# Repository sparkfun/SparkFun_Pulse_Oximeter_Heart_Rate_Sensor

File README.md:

SparkFun Pulse Oximeter and Heart Rate Monitor 
========================================

[*SparkFun Pulse Oximeter and Heart Rate Monitor (SEN-15291)*](https://www.sparkfun.com/products/15219)

The SparkFun Pulse Oximeter and Heart-Rate Sensor is an I&sup2;C based [biometric](https://en.wikipedia.org/wiki/Biometrics) sensor, utilizing two chips from Maxim Integrated: 
the MAX32664 Bio Metric Sensor Hub and the MAX30101 Pulse Oximetry and Heart-Rate Module.

The MAX30101 does all the sensing by utilizing its' internal LEDs to bounce light off the arteries and arterioles in your finger's subcutaneous layer and sensing how much light 
is absorbed with its' photodetectors . This is known as [photoplethysmography](https://en.wikipedia.org/wiki/Photoplethysmogram). This data is passed onto and analyzed by the 
MAX32664 which applies its' algorithms to determine heart rate and blood oxygen saturation (SpO2). The embedded algorithm uses digital filtering, pressure/position compensation, 
advanced R-wave detection and automatic gain control to determine the heart rate in beats per minute while minimizing power.  SpO2 results are reported as percentage of hemoglobin 
that is saturated with oxygen. It also provides useful information such as the sensor's confidence in its' reportings as well as a handy finger detection data point. To get the 
most out of the sensor we've written an Arduino Library to make it easy to adjust all the possible configurations.

Repository Contents
-------------------

* **/Documentation** - Data sheets and additional product information.
* **/Firmware** - Programming File for the MAX32664 
* **/Hardware** - Eagle design files (.brd, .sch)
* **/Production** - Production panel files (.brd)

Documentation
--------------
* **[Arduino Library](https://github.com/sparkfun/SparkFun_Bio_Sensor_Hub_Library)** - Arduino Library with Example Sketches
* **[Hookup Guide](https://learn.sparkfun.com/tutorials/sparkfun-pulse-oximeter-and-heart-rate-monitor-hookup-guide)** - Basic hookup guide for the SparkFun Pulse Oximeter and Heart Rate Sensor.

Product Versions
----------------
* [SEN-15291](https://www.sparkfun.com/products/15219)- SparkFun Version 1.0

License Information
-------------------

This product is _**open source**_! 

Please review the LICENSE.md file for license information. 

If you have any questions or concerns on licensing, please contact technical support on our [SparkFun forums](https://forum.sparkfun.com/viewforum.php?f=152).

Distributed as-is; no warranty is given.

- Your friends at SparkFun.

_<COLLABORATION CREDIT>_

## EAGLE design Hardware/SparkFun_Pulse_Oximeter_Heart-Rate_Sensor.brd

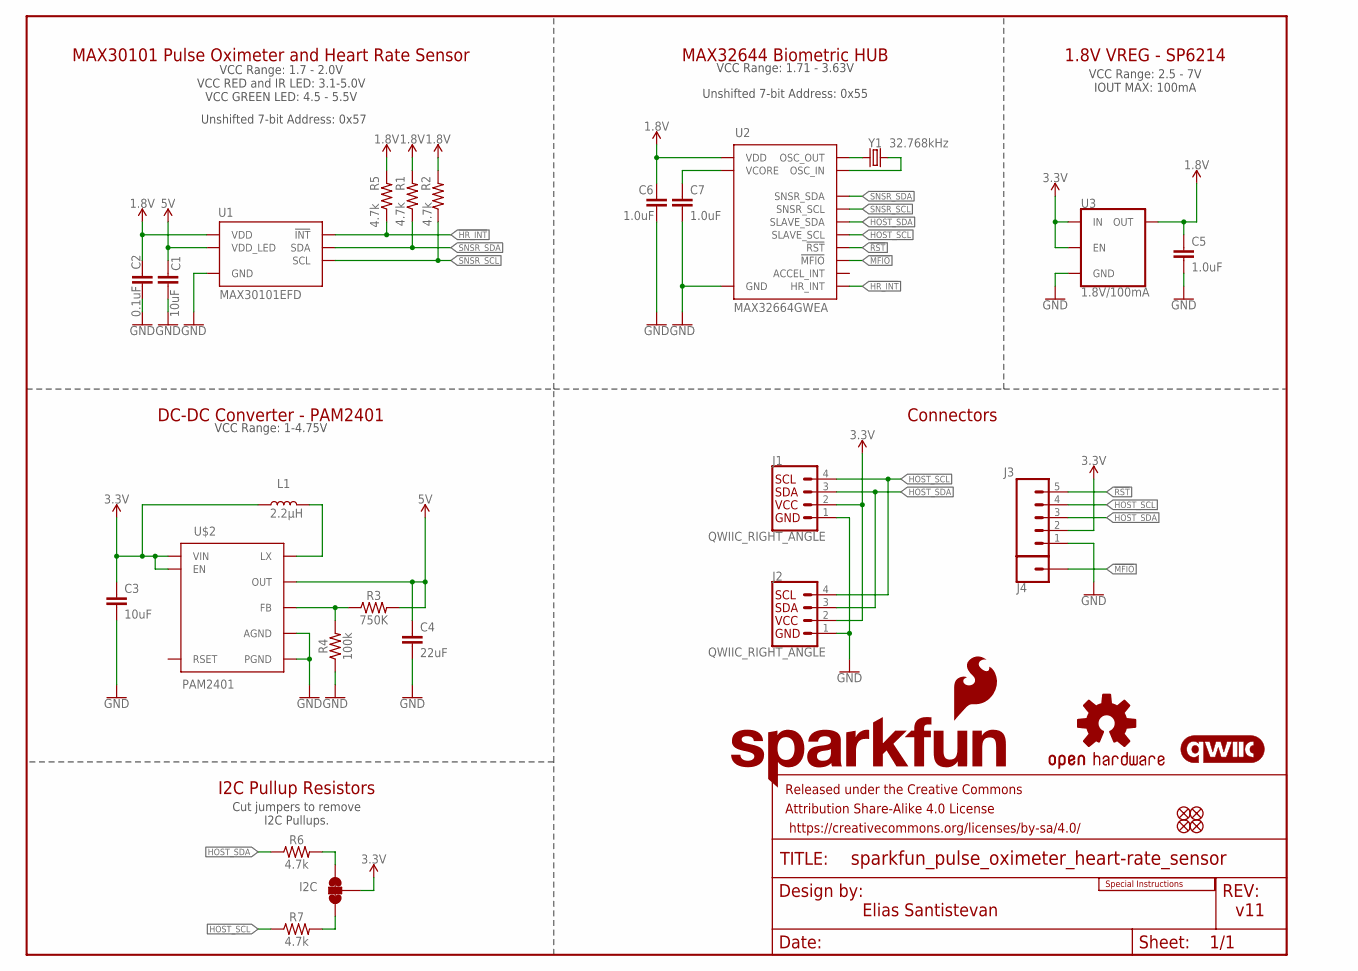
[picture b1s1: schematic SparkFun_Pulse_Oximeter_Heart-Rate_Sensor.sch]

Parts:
C1, C3: 10uF; 0603
C2: 0.1uF; 0402-TIGHT
C4: 22uF; 0805
C5: 1.0uF; 0603
C6, C7: 1.0uF; 0402-TIGHT
FD1, FD2, FD3, FD4: FIDUCIALUFIDUCIAL; FIDUCIAL-MICRO
FRAME1: FRAME-LETTER; CREATIVE_COMMONS
I2C: JUMPER-SMT_3_2-NC_TRACE_SILK; SMT-JUMPER_3_2-NC_TRACE_SILK
J1, J2: QWIIC_RIGHT_ANGLE; JST04_1MM_RA
J3: CONN_05NO_SILK; 1X05_NO_SILK
J4: CONN_01PTH_NO_SILK_YES_STOP; 1X01_NO_SILK
L1: 2.2μH; 0806
LOGO1: SFE_LOGO_FLAME.1_INCH; SFE_LOGO_FLAME_.1
LOGO2: OSHW-LOGOMINI; OSHW-LOGO-MINI
LOGO3: SFE_LOGO_NAME.1_INCH; SFE_LOGO_NAME_.1
LOGO4: SPECIAL_INSTRUCTIONS-ORDERING; ORDERING_INSTRUCTIONS
LOGO5: QWIIC_LOGO_4MM; QWIIC_4MM
R1, R2, R5, R6, R7: 4.7k; 0603
R3: 750K; 0603
R4: 100k; 0402-TIGHT
U1: MAX30101EFD; 14_PIN_OESIP
U2: MAX32664GWEA; 16_PIN_WLP
U3: 1.8V/100mA; SC70
U$2: PAM2401; MSOP8
Y1: 32.768kHz; CRYSTAL-SMD-3.2X1.5MM

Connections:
1.8V: C2.1, C5.1, C6.1, R1.2, R2.2, R5.2, U1.P11 (VDD), U2.3 (VDD), U3.5 (OUT)
3.3V: C3.1, I2C.2, J1.2, J2.2, J3.2, L1.1, U3.1 (IN), U3.3 (EN), U$2.2 (EN), U$2.3 (VIN)
5V: C1.1, C4.1, R3.2, U1.P9 (VDD_LED), U1.P10 (VDD_LED), U$2.7 (OUT)
!HR_INT: R5.1, U1.P13 (!INT), U2.6 (HR_INT)
!MFIO: J4.1, U2.16 (!MFIO)
!RST: J3.5, U2.12 (!RST)
GND: C1.2, C2.2, C3.2, C4.2, C5.2, C6.2, C7.2, J1.1, J2.1, J3.1, R4.1, U1.P4 (GND), U1.P12 (GND), U2.13 (GND), U3.2 (GND), U$2.4 (AGND), U$2.8 (PGND)
HOST_SCL: J1.4, J2.4, J3.4, R7.1, U2.10 (SLAVE_SCL)
HOST_SDA: J1.3, J2.3, J3.3, R6.1, U2.9 (SLAVE_SDA)
unnamed: C7.1, U2.4 (VCORE)
unnamed: R3.1, R4.2, U$2.5 (FB)
unnamed: L1.2, U$2.1 (LX)
unnamed: I2C.3, R6.2
unnamed: I2C.1, R7.2
unnamed: U2.1 (OSC_OUT), Y1.P$1 (1)
unnamed: U2.2 (OSC_IN), Y1.P$2 (2)
SNSR_SCL: R2.1, U1.P2 (SCL), U2.5 (SNSR_SCL)
SNSR_SDA: R1.1, U1.P3 (SDA), U2.14 (SNSR_SDA)

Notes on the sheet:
Elias Santistevan
v11
VCC Range: 1.71 - 3.63V
Unshifted 7-bit Address: 0x55
MAX30101 Pulse Oximeter and Heart Rate Sensor
MAX32644 Biometric HUB
1.8V VREG - SP6214
DC-DC Converter - PAM2401
Connectors
I2C Pullup Resistors
VCC Range: 1.7 - 2.0V VCC RED and IR LED: 3.1-5.0V VCC GREEN LED: 4.5 - 5.5V
Unshifted 7-bit Address: 0x57
VCC Range: 2.5 - 7V IOUT MAX: 100mA
VCC Range: 1-4.75V
Cut jumpers to remove I2C Pullups.

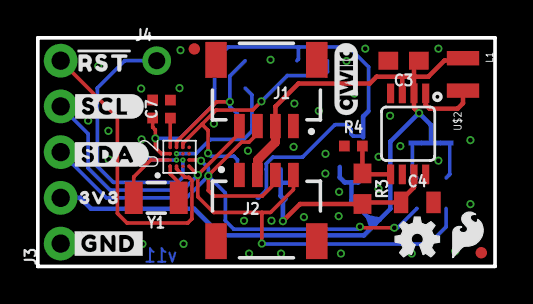
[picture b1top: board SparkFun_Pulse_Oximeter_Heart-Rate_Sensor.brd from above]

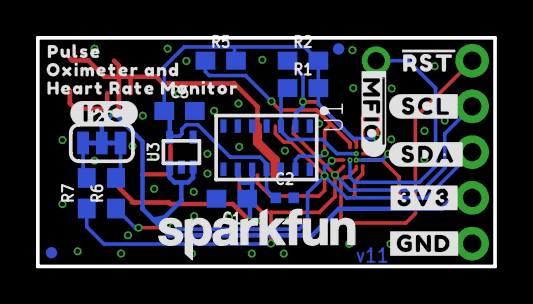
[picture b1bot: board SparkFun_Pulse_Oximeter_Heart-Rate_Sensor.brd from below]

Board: 2 copper layers, 25.4 x 12.7 mm, 50 parts (24 on the bottom side), 18 nets.

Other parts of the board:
U$1: #I2C#1348
U$3, U$5: #GND#0
U$4: #SCL#7
U$6, U$12: #RST#32
U$7: 3V338
U$8: #SDA#10
U$9: #3V3#1
U$10: #SDA#9
U$11: #SCL#9
U$13: ##MFIO##12
U$17: PULSE35
U$20: OXIMETER_AND36
U$21: HEART_RATE_MONITOR37

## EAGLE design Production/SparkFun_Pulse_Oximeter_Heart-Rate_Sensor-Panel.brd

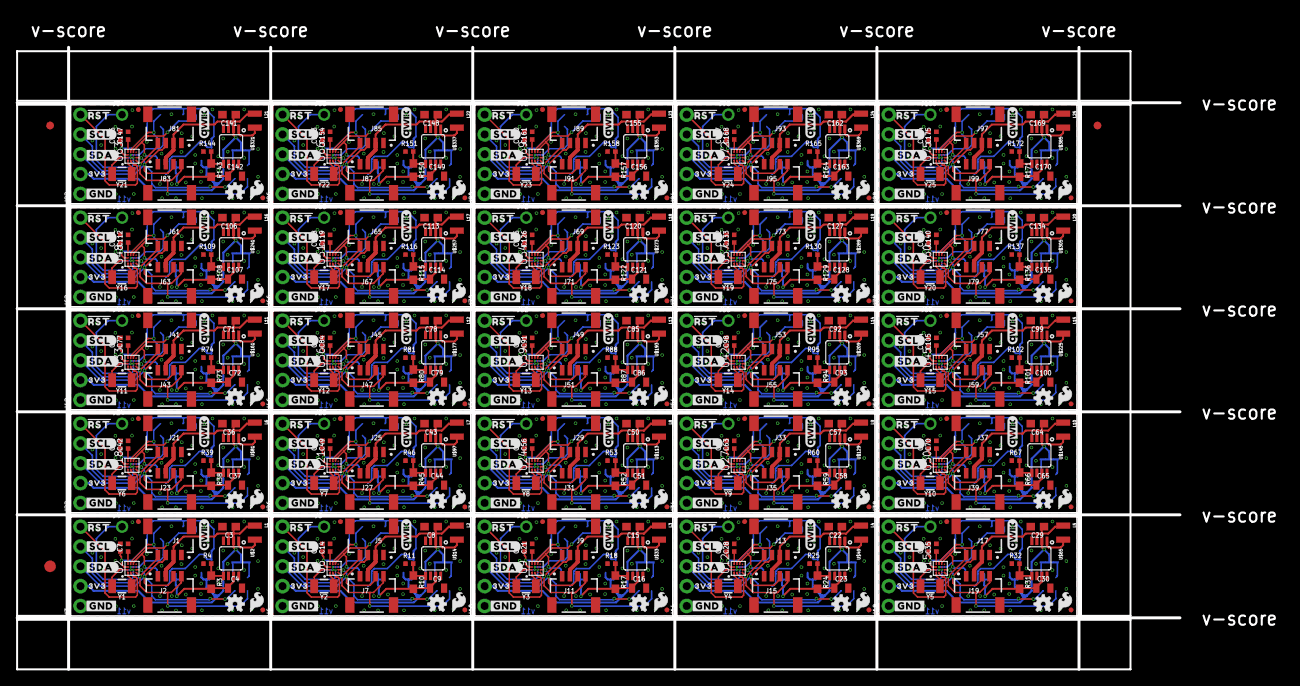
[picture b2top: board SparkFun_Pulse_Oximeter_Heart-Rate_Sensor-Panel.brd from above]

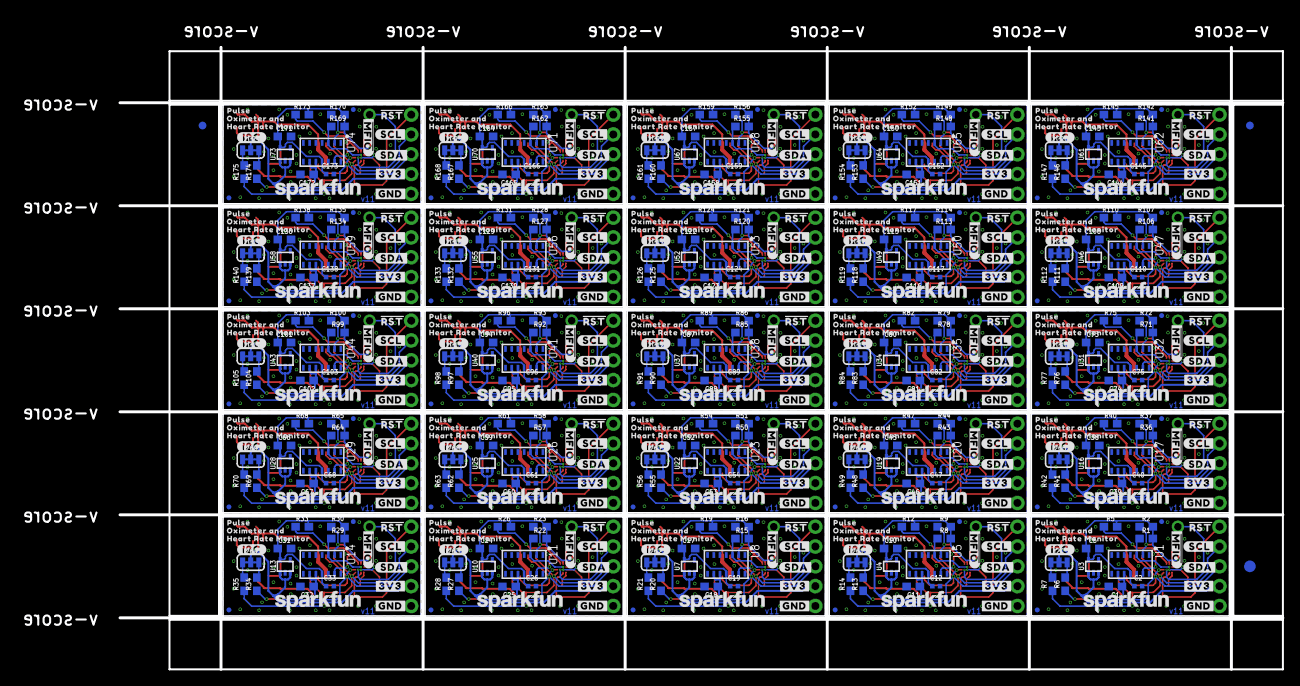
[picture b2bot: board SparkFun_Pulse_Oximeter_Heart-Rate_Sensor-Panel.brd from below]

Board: 2 copper layers, 162.3 x 83.6 mm, 1206 parts (603 on the bottom side), 450 nets.

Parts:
C1, C3, C8, C11, C15, C18, C22, C25, C29, C32, C36, C39, C43, C46, C50, C53, C57, C60, C64, C67, C71, C74, C78, C81, C85, C88, C92, C95, C99, C102, C106, C109, C113, C116, C120, C123, C127, C130, C134, C137, C141, C144, C148, C151, C155, C158, C162, C165, C169, C172: 10uF; 0603
C2, C12, C19, C26, C33, C40, C47, C54, C61, C68, C75, C82, C89, C96, C103, C110, C117, C124, C131, C138, C145, C152, C159, C166, C173: 0.1uF; 0402-TIGHT
C4, C9, C16, C23, C30, C37, C44, C51, C58, C65, C72, C79, C86, C93, C100, C107, C114, C121, C128, C135, C142, C149, C156, C163, C170: 22uF; 0805
C5, C10, C17, C24, C31, C38, C45, C52, C59, C66, C73, C80, C87, C94, C101, C108, C115, C122, C129, C136, C143, C150, C157, C164, C171: 1.0uF; 0603
C6, C7, C13, C14, C20, C21, C27, C28, C34, C35, C41, C42, C48, C49, C55, C56, C62, C63, C69, C70, C76, C77, C83, C84, C90, C91, C97, C98, C104, C105, C111, C112, C118, C119, C125, C126, C132, C133, C139, C140, C146, C147, C153, C154, C160, C161, C167, C168, C174, C175: 1.0uF; 0402-TIGHT
E$1, E$2, E$3, E$4: FIDUCIAL-1X2
E$5, E$6: FIDUCIAL-1.5X3
FD1, FD2, FD3, FD4, FD5, FD6, FD7, FD8, FD9, FD10, FD11, FD12, FD13, FD14, FD15, FD16, FD17, FD18, FD19, FD20, FD21, FD22, FD23, FD24, FD25, FD26, FD27, FD28, FD29, FD30, FD31, FD32, FD33, FD34, FD35, FD36, FD37, FD38, FD39, FD40, FD41, FD42, FD43, FD44, FD45, FD46, FD47, FD48, FD49, FD50, FD51, FD52, FD53, FD54, FD55, FD56, FD57, FD58, FD59, FD60, FD61, FD62, FD63, FD64, FD65, FD66, FD67, FD68, FD69, FD70, FD71, FD72, FD73, FD74, FD75, FD76, FD77, FD78, FD79, FD80, FD81, FD82, FD83, FD84, FD85, FD86, FD87, FD88, FD89, FD90, FD91, FD92, FD93, FD94, FD95, FD96, FD97, FD98, FD99, FD100: FIDUCIALUFIDUCIAL; FIDUCIAL-MICRO
I2C, I2C1, I2C2, I2C3, I2C4, I2C5, I2C6, I2C7, I2C8, I2C9, I2C10, I2C11, I2C12, I2C13, I2C14, I2C15, I2C16, I2C17, I2C18, I2C19, I2C20, I2C21, I2C22, I2C23, I2C24: JUMPER-SMT_3_2-NC_TRACE_SILK; SMT-JUMPER_3_2-NC_TRACE_SILK
J1, J2, J5, J7, J9, J11, J13, J15, J17, J19, J21, J23, J25, J27, J29, J31, J33, J35, J37, J39, J41, J43, J45, J47, J49, J51, J53, J55, J57, J59, J61, J63, J65, J67, J69, J71, J73, J75, J77, J79, J81, J83, J85, J87, J89, J91, J93, J95, J97, J99: QWIIC_RIGHT_ANGLE; JST04_1MM_RA
J3, J6, J10, J14, J18, J22, J26, J30, J34, J38, J42, J46, J50, J54, J58, J62, J66, J70, J74, J78, J82, J86, J90, J94, J98: 1X05_NO_SILK
J4, J8, J12, J16, J20, J24, J28, J32, J36, J40, J44, J48, J52, J56, J60, J64, J68, J72, J76, J80, J84, J88, J92, J96, J100: 1X01_NO_SILK
L1, L2, L3, L4, L5, L6, L7, L8, L9, L10, L11, L12, L13, L14, L15, L16, L17, L18, L19, L20, L21, L22, L23, L24, L25: 2.2μH; 0806
LOGO1, LOGO4, LOGO9, LOGO13, LOGO17, LOGO21, LOGO25, LOGO29, LOGO33, LOGO37, LOGO41, LOGO45, LOGO49, LOGO53, LOGO57, LOGO61, LOGO65, LOGO69, LOGO73, LOGO77, LOGO81, LOGO85, LOGO89, LOGO93, LOGO97: SFE_LOGO_FLAME.1_INCH; SFE_LOGO_FLAME_.1
LOGO2, LOGO6, LOGO10, LOGO14, LOGO18, LOGO22, LOGO26, LOGO30, LOGO34, LOGO38, LOGO42, LOGO46, LOGO50, LOGO54, LOGO58, LOGO62, LOGO66, LOGO70, LOGO74, LOGO78, LOGO82, LOGO86, LOGO90, LOGO94, LOGO98: OSHW-LOGOMINI; OSHW-LOGO-MINI
LOGO3, LOGO7, LOGO11, LOGO15, LOGO19, LOGO23, LOGO27, LOGO31, LOGO35, LOGO39, LOGO43, LOGO47, LOGO51, LOGO55, LOGO59, LOGO63, LOGO67, LOGO71, LOGO75, LOGO79, LOGO83, LOGO87, LOGO91, LOGO95, LOGO99: SFE_LOGO_NAME.1_INCH; SFE_LOGO_NAME_.1
LOGO5, LOGO8, LOGO12, LOGO16, LOGO20, LOGO24, LOGO28, LOGO32, LOGO36, LOGO40, LOGO44, LOGO48, LOGO52, LOGO56, LOGO60, LOGO64, LOGO68, LOGO72, LOGO76, LOGO80, LOGO84, LOGO88, LOGO92, LOGO96, LOGO100: QWIIC_LOGO_4MM; QWIIC_4MM
R1, R2, R5, R6, R7, R8, R9, R12, R13, R14, R15, R16, R19, R20, R21, R22, R23, R26, R27, R28, R29, R30, R33, R34, R35, R36, R37, R40, R41, R42, R43, R44, R47, R48, R49, R50, R51, R54, R55, R56, R57, R58, R61, R62, R63, R64, R65, R68, R69, R70, R71, R72, R75, R76, R77, R78, R79, R82, R83, R84, R85, R86, R89, R90, R91, R92, R93, R96, R97, R98, R99, R100, R103, R104, R105, R106, R107, R110, R111, R112, R113, R114, R117, R118, R119, R120, R121, R124, R125, R126, R127, R128, R131, R132, R133, R134, R135, R138, R139, R140, R141, R142, R145, R146, R147, R148, R149, R152, R153, R154, R155, R156, R159, R160, R161, R162, R163, R166, R167, R168, R169, R170, R173, R174, R175: 4.7k; 0603
R3, R10, R17, R24, R31, R38, R45, R52, R59, R66, R73, R80, R87, R94, R101, R108, R115, R122, R129, R136, R143, R150, R157, R164, R171: 750K; 0603
R4, R11, R18, R25, R32, R39, R46, R53, R60, R67, R74, R81, R88, R95, R102, R109, R116, R123, R130, R137, R144, R151, R158, R165, R172: 100k; 0402-TIGHT
U1, U5, U8, U11, U14, U17, U20, U23, U26, U29, U32, U35, U38, U41, U44, U47, U50, U53, U56, U59, U62, U65, U68, U71, U74: MAX30101EFD; 14_PIN_OESIP
U2, U6, U9, U12, U15, U18, U21, U24, U27, U30, U33, U36, U39, U42, U45, U48, U51, U54, U57, U60, U63, U66, U69, U72, U75: MAX32664GWEA; 16_PIN_WLP
U3, U4, U7, U10, U13, U16, U19, U22, U25, U28, U31, U34, U37, U40, U43, U46, U49, U52, U55, U58, U61, U64, U67, U70, U73: 1.8V/100mA; SC70
U$1, U$27, U$43, U$59, U$75, U$91, U$107, U$123, U$139, U$155, U$171, U$187, U$203, U$219, U$235, U$251, U$267, U$283, U$299, U$315, U$331, U$347, U$363, U$379, U$395: #I2C#1348
U$2, U$14, U$33, U$49, U$65, U$81, U$97, U$113, U$129, U$145, U$161, U$177, U$193, U$209, U$225, U$241, U$257, U$273, U$289, U$305, U$321, U$337, U$353, U$369, U$385: PAM2401; MSOP8
U$3, U$5, U$19, U$22, U$37, U$38, U$53, U$54, U$69, U$70, U$85, U$86, U$101, U$102, U$117, U$118, U$133, U$134, U$149, U$150, U$165, U$166, U$181, U$182, U$197, U$198, U$213, U$214, U$229, U$230, U$245, U$246, U$261, U$262, U$277, U$278, U$293, U$294, U$309, U$310, U$325, U$326, U$341, U$342, U$357, U$358, U$373, U$374, U$389, U$390: #GND#0
U$4, U$16, U$35, U$51, U$67, U$83, U$99, U$115, U$131, U$147, U$163, U$179, U$195, U$211, U$227, U$243, U$259, U$275, U$291, U$307, U$323, U$339, U$355, U$371, U$387: #SCL#7
U$6, U$12, U$15, U$26, U$34, U$42, U$50, U$58, U$66, U$74, U$82, U$90, U$98, U$106, U$114, U$122, U$130, U$138, U$146, U$154, U$162, U$170, U$178, U$186, U$194, U$202, U$210, U$218, U$226, U$234, U$242, U$250, U$258, U$266, U$274, U$282, U$290, U$298, U$306, U$314, U$322, U$330, U$338, U$346, U$354, U$362, U$370, U$378, U$386, U$394: #RST#32
U$7, U$28, U$44, U$60, U$76, U$92, U$108, U$124, U$140, U$156, U$172, U$188, U$204, U$220, U$236, U$252, U$268, U$284, U$300, U$316, U$332, U$348, U$364, U$380, U$396: 3V338
U$8, U$18, U$36, U$52, U$68, U$84, U$100, U$116, U$132, U$148, U$164, U$180, U$196, U$212, U$228, U$244, U$260, U$276, U$292, U$308, U$324, U$340, U$356, U$372, U$388: #SDA#10
U$9, U$23, U$39, U$55, U$71, U$87, U$103, U$119, U$135, U$151, U$167, U$183, U$199, U$215, U$231, U$247, U$263, U$279, U$295, U$311, U$327, U$343, U$359, U$375, U$391: #3V3#1
U$10, U$24, U$40, U$56, U$72, U$88, U$104, U$120, U$136, U$152, U$168, U$184, U$200, U$216, U$232, U$248, U$264, U$280, U$296, U$312, U$328, U$344, U$360, U$376, U$392: #SDA#9
U$11, U$25, U$41, U$57, U$73, U$89, U$105, U$121, U$137, U$153, U$169, U$185, U$201, U$217, U$233, U$249, U$265, U$281, U$297, U$313, U$329, U$345, U$361, U$377, U$393: #SCL#9
U$13, U$29, U$45, U$61, U$77, U$93, U$109, U$125, U$141, U$157, U$173, U$189, U$205, U$221, U$237, U$253, U$269, U$285, U$301, U$317, U$333, U$349, U$365, U$381, U$397: ##MFIO##12
U$17, U$30, U$46, U$62, U$78, U$94, U$110, U$126, U$142, U$158, U$174, U$190, U$206, U$222, U$238, U$254, U$270, U$286, U$302, U$318, U$334, U$350, U$366, U$382, U$398: PULSE35
U$20, U$31, U$47, U$63, U$79, U$95, U$111, U$127, U$143, U$159, U$175, U$191, U$207, U$223, U$239, U$255, U$271, U$287, U$303, U$319, U$335, U$351, U$367, U$383, U$399: OXIMETER_AND36
U$21, U$32, U$48, U$64, U$80, U$96, U$112, U$128, U$144, U$160, U$176, U$192, U$208, U$224, U$240, U$256, U$272, U$288, U$304, U$320, U$336, U$352, U$368, U$384, U$400: HEART_RATE_MONITOR37
Y1, Y2, Y3, Y4, Y5, Y6, Y7, Y8, Y9, Y10, Y11, Y12, Y13, Y14, Y15, Y16, Y17, Y18, Y19, Y20, Y21, Y22, Y23, Y24, Y25: 32.768kHz; CRYSTAL-SMD-3.2X1.5MM

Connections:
1.8V: C2.1, C5.1, C6.1, R1.2, R2.2, R5.2, U1.P11, U2.3, U3.5
1.8V1: C10.1, C12.1, C13.1, R8.2, R9.2, R12.2, U4.5, U5.P11, U6.3
1.8V2: C17.1, C19.1, C20.1, R15.2, R16.2, R19.2, U7.5, U8.P11, U9.3
1.8V3: C24.1, C26.1, C27.1, R22.2, R23.2, R26.2, U10.5, U11.P11, U12.3
1.8V4: C31.1, C33.1, C34.1, R29.2, R30.2, R33.2, U13.5, U14.P11, U15.3
1.8V5: C38.1, C40.1, C41.1, R36.2, R37.2, R40.2, U16.5, U17.P11, U18.3
1.8V6: C45.1, C47.1, C48.1, R43.2, R44.2, R47.2, U19.5, U20.P11, U21.3
1.8V7: C52.1, C54.1, C55.1, R50.2, R51.2, R54.2, U22.5, U23.P11, U24.3
1.8V8: C59.1, C61.1, C62.1, R57.2, R58.2, R61.2, U25.5, U26.P11, U27.3
1.8V9: C66.1, C68.1, C69.1, R64.2, R65.2, R68.2, U28.5, U29.P11, U30.3
1.8V10: C73.1, C75.1, C76.1, R71.2, R72.2, R75.2, U31.5, U32.P11, U33.3
1.8V11: C80.1, C82.1, C83.1, R78.2, R79.2, R82.2, U34.5, U35.P11, U36.3
1.8V12: C87.1, C89.1, C90.1, R85.2, R86.2, R89.2, U37.5, U38.P11, U39.3
1.8V13: C94.1, C96.1, C97.1, R92.2, R93.2, R96.2, U40.5, U41.P11, U42.3
1.8V14: C101.1, C103.1, C104.1, R99.2, R100.2, R103.2, U43.5, U44.P11, U45.3
1.8V15: C108.1, C110.1, C111.1, R106.2, R107.2, R110.2, U46.5, U47.P11, U48.3
1.8V16: C115.1, C117.1, C118.1, R113.2, R114.2, R117.2, U49.5, U50.P11, U51.3
1.8V17: C122.1, C124.1, C125.1, R120.2, R121.2, R124.2, U52.5, U53.P11, U54.3
1.8V18: C129.1, C131.1, C132.1, R127.2, R128.2, R131.2, U55.5, U56.P11, U57.3
1.8V19: C136.1, C138.1, C139.1, R134.2, R135.2, R138.2, U58.5, U59.P11, U60.3
1.8V20: C143.1, C145.1, C146.1, R141.2, R142.2, R145.2, U61.5, U62.P11, U63.3
1.8V21: C150.1, C152.1, C153.1, R148.2, R149.2, R152.2, U64.5, U65.P11, U66.3
1.8V22: C157.1, C159.1, C160.1, R155.2, R156.2, R159.2, U67.5, U68.P11, U69.3
1.8V23: C164.1, C166.1, C167.1, R162.2, R163.2, R166.2, U70.5, U71.P11, U72.3
1.8V24: C171.1, C173.1, C174.1, R169.2, R170.2, R173.2, U73.5, U74.P11, U75.3
3.3V: C3.1, I2C.2, J1.2, J2.2, J3.2, L1.1, U3.1, U3.3, U$2.2, U$2.3
3.3V1: C8.1, I2C1.2, J5.2, J6.2, J7.2, L2.1, U4.1, U4.3, U$14.2, U$14.3
3.3V2: C15.1, I2C2.2, J9.2, J10.2, J11.2, L3.1, U7.1, U7.3, U$33.2, U$33.3
3.3V3: C22.1, I2C3.2, J13.2, J14.2, J15.2, L4.1, U10.1, U10.3, U$49.2, U$49.3
3.3V4: C29.1, I2C4.2, J17.2, J18.2, J19.2, L5.1, U13.1, U13.3, U$65.2, U$65.3
3.3V5: C36.1, I2C5.2, J21.2, J22.2, J23.2, L6.1, U16.1, U16.3, U$81.2, U$81.3
3.3V6: C43.1, I2C6.2, J25.2, J26.2, J27.2, L7.1, U19.1, U19.3, U$97.2, U$97.3
3.3V7: C50.1, I2C7.2, J29.2, J30.2, J31.2, L8.1, U22.1, U22.3, U$113.2, U$113.3
3.3V8: C57.1, I2C8.2, J33.2, J34.2, J35.2, L9.1, U25.1, U25.3, U$129.2, U$129.3
3.3V9: C64.1, I2C9.2, J37.2, J38.2, J39.2, L10.1, U28.1, U28.3, U$145.2, U$145.3
3.3V10: C71.1, I2C10.2, J41.2, J42.2, J43.2, L11.1, U31.1, U31.3, U$161.2, U$161.3
3.3V11: C78.1, I2C11.2, J45.2, J46.2, J47.2, L12.1, U34.1, U34.3, U$177.2, U$177.3
3.3V12: C85.1, I2C12.2, J49.2, J50.2, J51.2, L13.1, U37.1, U37.3, U$193.2, U$193.3
3.3V13: C92.1, I2C13.2, J53.2, J54.2, J55.2, L14.1, U40.1, U40.3, U$209.2, U$209.3
3.3V14: C99.1, I2C14.2, J57.2, J58.2, J59.2, L15.1, U43.1, U43.3, U$225.2, U$225.3
3.3V15: C106.1, I2C15.2, J61.2, J62.2, J63.2, L16.1, U46.1, U46.3, U$241.2, U$241.3
3.3V16: C113.1, I2C16.2, J65.2, J66.2, J67.2, L17.1, U49.1, U49.3, U$257.2, U$257.3
3.3V17: C120.1, I2C17.2, J69.2, J70.2, J71.2, L18.1, U52.1, U52.3, U$273.2, U$273.3
3.3V18: C127.1, I2C18.2, J73.2, J74.2, J75.2, L19.1, U55.1, U55.3, U$289.2, U$289.3
3.3V19: C134.1, I2C19.2, J77.2, J78.2, J79.2, L20.1, U58.1, U58.3, U$305.2, U$305.3
3.3V20: C141.1, I2C20.2, J81.2, J82.2, J83.2, L21.1, U61.1, U61.3, U$321.2, U$321.3
3.3V21: C148.1, I2C21.2, J85.2, J86.2, J87.2, L22.1, U64.1, U64.3, U$337.2, U$337.3
3.3V22: C155.1, I2C22.2, J89.2, J90.2, J91.2, L23.1, U67.1, U67.3, U$353.2, U$353.3
3.3V23: C162.1, I2C23.2, J93.2, J94.2, J95.2, L24.1, U70.1, U70.3, U$369.2, U$369.3
3.3V24: C169.1, I2C24.2, J97.2, J98.2, J99.2, L25.1, U73.1, U73.3, U$385.2, U$385.3
5V: C1.1, C4.1, R3.2, U1.P9, U1.P10, U$2.7
5V1: C9.1, C11.1, R10.2, U5.P9, U5.P10, U$14.7
5V2: C16.1, C18.1, R17.2, U8.P9, U8.P10, U$33.7
5V3: C23.1, C25.1, R24.2, U11.P9, U11.P10, U$49.7
5V4: C30.1, C32.1, R31.2, U14.P9, U14.P10, U$65.7
5V5: C37.1, C39.1, R38.2, U17.P9, U17.P10, U$81.7
5V6: C44.1, C46.1, R45.2, U20.P9, U20.P10, U$97.7
5V7: C51.1, C53.1, R52.2, U23.P9, U23.P10, U$113.7
5V8: C58.1, C60.1, R59.2, U26.P9, U26.P10, U$129.7
5V9: C65.1, C67.1, R66.2, U29.P9, U29.P10, U$145.7
5V10: C72.1, C74.1, R73.2, U32.P9, U32.P10, U$161.7
5V11: C79.1, C81.1, R80.2, U35.P9, U35.P10, U$177.7
5V12: C86.1, C88.1, R87.2, U38.P9, U38.P10, U$193.7
5V13: C93.1, C95.1, R94.2, U41.P9, U41.P10, U$209.7
5V14: C100.1, C102.1, R101.2, U44.P9, U44.P10, U$225.7
5V15: C107.1, C109.1, R108.2, U47.P9, U47.P10, U$241.7
5V16: C114.1, C116.1, R115.2, U50.P9, U50.P10, U$257.7
5V17: C121.1, C123.1, R122.2, U53.P9, U53.P10, U$273.7
5V18: C128.1, C130.1, R129.2, U56.P9, U56.P10, U$289.7
5V19: C135.1, C137.1, R136.2, U59.P9, U59.P10, U$305.7
5V20: C142.1, C144.1, R143.2, U62.P9, U62.P10, U$321.7
5V21: C149.1, C151.1, R150.2, U65.P9, U65.P10, U$337.7
5V22: C156.1, C158.1, R157.2, U68.P9, U68.P10, U$353.7
5V23: C163.1, C165.1, R164.2, U71.P9, U71.P10, U$369.7
5V24: C170.1, C172.1, R171.2, U74.P9, U74.P10, U$385.7
!HR_INT: R5.1, U1.P13, U2.6
!HR_INT1: R12.1, U5.P13, U6.6
!HR_INT2: R19.1, U8.P13, U9.6
!HR_INT3: R26.1, U11.P13, U12.6
!HR_INT4: R33.1, U14.P13, U15.6
!HR_INT5: R40.1, U17.P13, U18.6
!HR_INT6: R47.1, U20.P13, U21.6
!HR_INT7: R54.1, U23.P13, U24.6
!HR_INT8: R61.1, U26.P13, U27.6
!HR_INT9: R68.1, U29.P13, U30.6
!HR_INT10: R75.1, U32.P13, U33.6
!HR_INT11: R82.1, U35.P13, U36.6
!HR_INT12: R89.1, U38.P13, U39.6
!HR_INT13: R96.1, U41.P13, U42.6
!HR_INT14: R103.1, U44.P13, U45.6
!HR_INT15: R110.1, U47.P13, U48.6
!HR_INT16: R117.1, U50.P13, U51.6
!HR_INT17: R124.1, U53.P13, U54.6
!HR_INT18: R131.1, U56.P13, U57.6
!HR_INT19: R138.1, U59.P13, U60.6
!HR_INT20: R145.1, U62.P13, U63.6
!HR_INT21: R152.1, U65.P13, U66.6
!HR_INT22: R159.1, U68.P13, U69.6
!HR_INT23: R166.1, U71.P13, U72.6
!HR_INT24: R173.1, U74.P13, U75.6
!MFIO: J4.1, U2.16
!MFIO1: J8.1, U6.16
!MFIO2: J12.1, U9.16
!MFIO3: J16.1, U12.16
!MFIO4: J20.1, U15.16
!MFIO5: J24.1, U18.16
!MFIO6: J28.1, U21.16
!MFIO7: J32.1, U24.16
!MFIO8: J36.1, U27.16
!MFIO9: J40.1, U30.16
!MFIO10: J44.1, U33.16
!MFIO11: J48.1, U36.16
!MFIO12: J52.1, U39.16
!MFIO13: J56.1, U42.16
!MFIO14: J60.1, U45.16
!MFIO15: J64.1, U48.16
!MFIO16: J68.1, U51.16
!MFIO17: J72.1, U54.16
!MFIO18: J76.1, U57.16
!MFIO19: J80.1, U60.16
!MFIO20: J84.1, U63.16
!MFIO21: J88.1, U66.16
!MFIO22: J92.1, U69.16
!MFIO23: J96.1, U72.16
!MFIO24: J100.1, U75.16
!RST: J3.5, U2.12
!RST1: J6.5, U6.12
!RST2: J10.5, U9.12
!RST3: J14.5, U12.12
!RST4: J18.5, U15.12
!RST5: J22.5, U18.12
!RST6: J26.5, U21.12
!RST7: J30.5, U24.12
!RST8: J34.5, U27.12
!RST9: J38.5, U30.12
!RST10: J42.5, U33.12
!RST11: J46.5, U36.12
!RST12: J50.5, U39.12
!RST13: J54.5, U42.12
!RST14: J58.5, U45.12
!RST15: J62.5, U48.12
!RST16: J66.5, U51.12
!RST17: J70.5, U54.12
!RST18: J74.5, U57.12
!RST19: J78.5, U60.12
!RST20: J82.5, U63.12
!RST21: J86.5, U66.12
!RST22: J90.5, U69.12
!RST23: J94.5, U72.12
!RST24: J98.5, U75.12
GND: C1.2, C2.2, C3.2, C4.2, C5.2, C6.2, C7.2, J1.1, J2.1, J3.1, R4.1, U1.P4, U1.P12, U2.13, U3.2, U$2.4, U$2.8
GND1: C8.2, C9.2, C10.2, C11.2, C12.2, C13.2, C14.2, J5.1, J6.1, J7.1, R11.1, U4.2, U5.P4, U5.P12, U6.13, U$14.4, U$14.8
GND2: C15.2, C16.2, C17.2, C18.2, C19.2, C20.2, C21.2, J9.1, J10.1, J11.1, R18.1, U7.2, U8.P4, U8.P12, U9.13, U$33.4, U$33.8
GND3: C22.2, C23.2, C24.2, C25.2, C26.2, C27.2, C28.2, J13.1, J14.1, J15.1, R25.1, U10.2, U11.P4, U11.P12, U12.13, U$49.4, U$49.8
GND4: C29.2, C30.2, C31.2, C32.2, C33.2, C34.2, C35.2, J17.1, J18.1, J19.1, R32.1, U13.2, U14.P4, U14.P12, U15.13, U$65.4, U$65.8
GND5: C36.2, C37.2, C38.2, C39.2, C40.2, C41.2, C42.2, J21.1, J22.1, J23.1, R39.1, U16.2, U17.P4, U17.P12, U18.13, U$81.4, U$81.8
GND6: C43.2, C44.2, C45.2, C46.2, C47.2, C48.2, C49.2, J25.1, J26.1, J27.1, R46.1, U19.2, U20.P4, U20.P12, U21.13, U$97.4, U$97.8
GND7: C50.2, C51.2, C52.2, C53.2, C54.2, C55.2, C56.2, J29.1, J30.1, J31.1, R53.1, U22.2, U23.P4, U23.P12, U24.13, U$113.4, U$113.8
GND8: C57.2, C58.2, C59.2, C60.2, C61.2, C62.2, C63.2, J33.1, J34.1, J35.1, R60.1, U25.2, U26.P4, U26.P12, U27.13, U$129.4, U$129.8
GND9: C64.2, C65.2, C66.2, C67.2, C68.2, C69.2, C70.2, J37.1, J38.1, J39.1, R67.1, U28.2, U29.P4, U29.P12, U30.13, U$145.4, U$145.8
GND10: C71.2, C72.2, C73.2, C74.2, C75.2, C76.2, C77.2, J41.1, J42.1, J43.1, R74.1, U31.2, U32.P4, U32.P12, U33.13, U$161.4, U$161.8
GND11: C78.2, C79.2, C80.2, C81.2, C82.2, C83.2, C84.2, J45.1, J46.1, J47.1, R81.1, U34.2, U35.P4, U35.P12, U36.13, U$177.4, U$177.8
GND12: C85.2, C86.2, C87.2, C88.2, C89.2, C90.2, C91.2, J49.1, J50.1, J51.1, R88.1, U37.2, U38.P4, U38.P12, U39.13, U$193.4, U$193.8
GND13: C92.2, C93.2, C94.2, C95.2, C96.2, C97.2, C98.2, J53.1, J54.1, J55.1, R95.1, U40.2, U41.P4, U41.P12, U42.13, U$209.4, U$209.8
GND14: C99.2, C100.2, C101.2, C102.2, C103.2, C104.2, C105.2, J57.1, J58.1, J59.1, R102.1, U43.2, U44.P4, U44.P12, U45.13, U$225.4, U$225.8
GND15: C106.2, C107.2, C108.2, C109.2, C110.2, C111.2, C112.2, J61.1, J62.1, J63.1, R109.1, U46.2, U47.P4, U47.P12, U48.13, U$241.4, U$241.8
GND16: C113.2, C114.2, C115.2, C116.2, C117.2, C118.2, C119.2, J65.1, J66.1, J67.1, R116.1, U49.2, U50.P4, U50.P12, U51.13, U$257.4, U$257.8
GND17: C120.2, C121.2, C122.2, C123.2, C124.2, C125.2, C126.2, J69.1, J70.1, J71.1, R123.1, U52.2, U53.P4, U53.P12, U54.13, U$273.4, U$273.8
GND18: C127.2, C128.2, C129.2, C130.2, C131.2, C132.2, C133.2, J73.1, J74.1, J75.1, R130.1, U55.2, U56.P4, U56.P12, U57.13, U$289.4, U$289.8
GND19: C134.2, C135.2, C136.2, C137.2, C138.2, C139.2, C140.2, J77.1, J78.1, J79.1, R137.1, U58.2, U59.P4, U59.P12, U60.13, U$305.4, U$305.8
GND20: C141.2, C142.2, C143.2, C144.2, C145.2, C146.2, C147.2, J81.1, J82.1, J83.1, R144.1, U61.2, U62.P4, U62.P12, U63.13, U$321.4, U$321.8
GND21: C148.2, C149.2, C150.2, C151.2, C152.2, C153.2, C154.2, J85.1, J86.1, J87.1, R151.1, U64.2, U65.P4, U65.P12, U66.13, U$337.4, U$337.8
GND22: C155.2, C156.2, C157.2, C158.2, C159.2, C160.2, C161.2, J89.1, J90.1, J91.1, R158.1, U67.2, U68.P4, U68.P12, U69.13, U$353.4, U$353.8
GND23: C162.2, C163.2, C164.2, C165.2, C166.2, C167.2, C168.2, J93.1, J94.1, J95.1, R165.1, U70.2, U71.P4, U71.P12, U72.13, U$369.4, U$369.8
GND24: C169.2, C170.2, C171.2, C172.2, C173.2, C174.2, C175.2, J97.1, J98.1, J99.1, R172.1, U73.2, U74.P4, U74.P12, U75.13, U$385.4, U$385.8
HOST_SCL: J1.4, J2.4, J3.4, R7.1, U2.10
HOST_SCL1: J5.4, J6.4, J7.4, R14.1, U6.10
HOST_SCL2: J9.4, J10.4, J11.4, R21.1, U9.10
HOST_SCL3: J13.4, J14.4, J15.4, R28.1, U12.10
HOST_SCL4: J17.4, J18.4, J19.4, R35.1, U15.10
HOST_SCL5: J21.4, J22.4, J23.4, R42.1, U18.10
HOST_SCL6: J25.4, J26.4, J27.4, R49.1, U21.10
HOST_SCL7: J29.4, J30.4, J31.4, R56.1, U24.10
HOST_SCL8: J33.4, J34.4, J35.4, R63.1, U27.10
HOST_SCL9: J37.4, J38.4, J39.4, R70.1, U30.10
HOST_SCL10: J41.4, J42.4, J43.4, R77.1, U33.10
HOST_SCL11: J45.4, J46.4, J47.4, R84.1, U36.10
HOST_SCL12: J49.4, J50.4, J51.4, R91.1, U39.10
HOST_SCL13: J53.4, J54.4, J55.4, R98.1, U42.10
HOST_SCL14: J57.4, J58.4, J59.4, R105.1, U45.10
HOST_SCL15: J61.4, J62.4, J63.4, R112.1, U48.10
HOST_SCL16: J65.4, J66.4, J67.4, R119.1, U51.10
HOST_SCL17: J69.4, J70.4, J71.4, R126.1, U54.10
HOST_SCL18: J73.4, J74.4, J75.4, R133.1, U57.10
HOST_SCL19: J77.4, J78.4, J79.4, R140.1, U60.10
HOST_SCL20: J81.4, J82.4, J83.4, R147.1, U63.10
HOST_SCL21: J85.4, J86.4, J87.4, R154.1, U66.10
HOST_SCL22: J89.4, J90.4, J91.4, R161.1, U69.10
HOST_SCL23: J93.4, J94.4, J95.4, R168.1, U72.10
HOST_SCL24: J97.4, J98.4, J99.4, R175.1, U75.10
HOST_SDA: J1.3, J2.3, J3.3, R6.1, U2.9
HOST_SDA1: J5.3, J6.3, J7.3, R13.1, U6.9
HOST_SDA2: J9.3, J10.3, J11.3, R20.1, U9.9
HOST_SDA3: J13.3, J14.3, J15.3, R27.1, U12.9
HOST_SDA4: J17.3, J18.3, J19.3, R34.1, U15.9
HOST_SDA5: J21.3, J22.3, J23.3, R41.1, U18.9
HOST_SDA6: J25.3, J26.3, J27.3, R48.1, U21.9
HOST_SDA7: J29.3, J30.3, J31.3, R55.1, U24.9
HOST_SDA8: J33.3, J34.3, J35.3, R62.1, U27.9
HOST_SDA9: J37.3, J38.3, J39.3, R69.1, U30.9
HOST_SDA10: J41.3, J42.3, J43.3, R76.1, U33.9
HOST_SDA11: J45.3, J46.3, J47.3, R83.1, U36.9
HOST_SDA12: J49.3, J50.3, J51.3, R90.1, U39.9
HOST_SDA13: J53.3, J54.3, J55.3, R97.1, U42.9
HOST_SDA14: J57.3, J58.3, J59.3, R104.1, U45.9
HOST_SDA15: J61.3, J62.3, J63.3, R111.1, U48.9
HOST_SDA16: J65.3, J66.3, J67.3, R118.1, U51.9
HOST_SDA17: J69.3, J70.3, J71.3, R125.1, U54.9
HOST_SDA18: J73.3, J74.3, J75.3, R132.1, U57.9
HOST_SDA19: J77.3, J78.3, J79.3, R139.1, U60.9
HOST_SDA20: J81.3, J82.3, J83.3, R146.1, U63.9
HOST_SDA21: J85.3, J86.3, J87.3, R153.1, U66.9
HOST_SDA22: J89.3, J90.3, J91.3, R160.1, U69.9
HOST_SDA23: J93.3, J94.3, J95.3, R167.1, U72.9
HOST_SDA24: J97.3, J98.3, J99.3, R174.1, U75.9
unnamed: C7.1, U2.4
unnamed: R3.1, R4.2, U$2.5
unnamed: L1.2, U$2.1
unnamed: I2C.3, R6.2
unnamed: I2C.1, R7.2
unnamed: U2.1, Y1.P$1
unnamed: U2.2, Y1.P$2
unnamed: R10.1, R11.2, U$14.5
unnamed: L2.2, U$14.1
unnamed: U6.1, Y2.P$1
unnamed: U6.2, Y2.P$2
unnamed: C14.1, U6.4
unnamed: I2C1.3, R13.2
unnamed: I2C1.1, R14.2
unnamed: R17.1, R18.2, U$33.5
unnamed: L3.2, U$33.1
unnamed: U9.1, Y3.P$1
unnamed: U9.2, Y3.P$2
unnamed: C21.1, U9.4
unnamed: I2C2.3, R20.2
unnamed: I2C2.1, R21.2
unnamed: R24.1, R25.2, U$49.5
unnamed: L4.2, U$49.1
unnamed: U12.1, Y4.P$1
unnamed: U12.2, Y4.P$2
unnamed: C28.1, U12.4
unnamed: I2C3.3, R27.2
unnamed: I2C3.1, R28.2
unnamed: R31.1, R32.2, U$65.5
unnamed: L5.2, U$65.1
unnamed: U15.1, Y5.P$1
unnamed: U15.2, Y5.P$2
unnamed: C35.1, U15.4
unnamed: I2C4.3, R34.2
unnamed: I2C4.1, R35.2
unnamed: R38.1, R39.2, U$81.5
unnamed: L6.2, U$81.1
unnamed: U18.1, Y6.P$1
unnamed: U18.2, Y6.P$2
unnamed: C42.1, U18.4
unnamed: I2C5.3, R41.2
unnamed: I2C5.1, R42.2
unnamed: R45.1, R46.2, U$97.5
unnamed: L7.2, U$97.1
unnamed: U21.1, Y7.P$1
unnamed: U21.2, Y7.P$2
unnamed: C49.1, U21.4
unnamed: I2C6.3, R48.2
unnamed: I2C6.1, R49.2
unnamed: R52.1, R53.2, U$113.5
unnamed: L8.2, U$113.1
unnamed: U24.1, Y8.P$1
unnamed: U24.2, Y8.P$2
unnamed: C56.1, U24.4
unnamed: I2C7.3, R55.2
unnamed: I2C7.1, R56.2
unnamed: R59.1, R60.2, U$129.5
unnamed: L9.2, U$129.1
unnamed: U27.1, Y9.P$1
unnamed: U27.2, Y9.P$2
unnamed: C63.1, U27.4
unnamed: I2C8.3, R62.2
unnamed: I2C8.1, R63.2
unnamed: R66.1, R67.2, U$145.5
unnamed: L10.2, U$145.1
unnamed: U30.1, Y10.P$1
unnamed: U30.2, Y10.P$2
unnamed: C70.1, U30.4
unnamed: I2C9.3, R69.2
unnamed: I2C9.1, R70.2
unnamed: R73.1, R74.2, U$161.5
unnamed: L11.2, U$161.1
unnamed: U33.1, Y11.P$1
unnamed: U33.2, Y11.P$2
unnamed: C77.1, U33.4
unnamed: I2C10.3, R76.2
unnamed: I2C10.1, R77.2
unnamed: R80.1, R81.2, U$177.5
unnamed: L12.2, U$177.1
unnamed: U36.1, Y12.P$1
unnamed: U36.2, Y12.P$2
unnamed: C84.1, U36.4
unnamed: I2C11.3, R83.2
unnamed: I2C11.1, R84.2
unnamed: R87.1, R88.2, U$193.5
unnamed: L13.2, U$193.1
unnamed: U39.1, Y13.P$1
unnamed: U39.2, Y13.P$2
unnamed: C91.1, U39.4
unnamed: I2C12.3, R90.2
unnamed: I2C12.1, R91.2
unnamed: R94.1, R95.2, U$209.5
unnamed: L14.2, U$209.1
unnamed: U42.1, Y14.P$1
unnamed: U42.2, Y14.P$2
unnamed: C98.1, U42.4
unnamed: I2C13.3, R97.2
unnamed: I2C13.1, R98.2
unnamed: R101.1, R102.2, U$225.5
unnamed: L15.2, U$225.1
unnamed: U45.1, Y15.P$1
unnamed: U45.2, Y15.P$2
unnamed: C105.1, U45.4
unnamed: I2C14.3, R104.2
unnamed: I2C14.1, R105.2
unnamed: R108.1, R109.2, U$241.5
unnamed: L16.2, U$241.1
unnamed: U48.1, Y16.P$1
unnamed: U48.2, Y16.P$2
unnamed: C112.1, U48.4
unnamed: I2C15.3, R111.2
unnamed: I2C15.1, R112.2
unnamed: R115.1, R116.2, U$257.5
unnamed: L17.2, U$257.1
unnamed: U51.1, Y17.P$1
unnamed: U51.2, Y17.P$2
unnamed: C119.1, U51.4
unnamed: I2C16.3, R118.2
unnamed: I2C16.1, R119.2
unnamed: R122.1, R123.2, U$273.5
unnamed: L18.2, U$273.1
unnamed: U54.1, Y18.P$1
unnamed: U54.2, Y18.P$2
unnamed: C126.1, U54.4
unnamed: I2C17.3, R125.2
unnamed: I2C17.1, R126.2
unnamed: R129.1, R130.2, U$289.5
unnamed: L19.2, U$289.1
unnamed: U57.1, Y19.P$1
unnamed: U57.2, Y19.P$2
unnamed: C133.1, U57.4
unnamed: I2C18.3, R132.2
unnamed: I2C18.1, R133.2
unnamed: R136.1, R137.2, U$305.5
unnamed: L20.2, U$305.1
unnamed: U60.1, Y20.P$1
unnamed: U60.2, Y20.P$2
unnamed: C140.1, U60.4
unnamed: I2C19.3, R139.2
unnamed: I2C19.1, R140.2
unnamed: R143.1, R144.2, U$321.5
unnamed: L21.2, U$321.1
unnamed: U63.1, Y21.P$1
unnamed: U63.2, Y21.P$2
unnamed: C147.1, U63.4
unnamed: I2C20.3, R146.2
unnamed: I2C20.1, R147.2
unnamed: R150.1, R151.2, U$337.5
unnamed: L22.2, U$337.1
unnamed: U66.1, Y22.P$1
unnamed: U66.2, Y22.P$2
unnamed: C154.1, U66.4
unnamed: I2C21.3, R153.2
unnamed: I2C21.1, R154.2
unnamed: R157.1, R158.2, U$353.5
unnamed: L23.2, U$353.1
unnamed: U69.1, Y23.P$1
unnamed: U69.2, Y23.P$2
unnamed: C161.1, U69.4
unnamed: I2C22.3, R160.2
unnamed: I2C22.1, R161.2
unnamed: R164.1, R165.2, U$369.5
unnamed: L24.2, U$369.1
unnamed: U72.1, Y24.P$1
unnamed: U72.2, Y24.P$2
unnamed: C168.1, U72.4
unnamed: I2C23.3, R167.2
unnamed: I2C23.1, R168.2
unnamed: R171.1, R172.2, U$385.5
unnamed: L25.2, U$385.1
unnamed: U75.1, Y25.P$1
unnamed: U75.2, Y25.P$2
unnamed: C175.1, U75.4
unnamed: I2C24.3, R174.2
unnamed: I2C24.1, R175.2
SNSR_SCL: R2.1, U1.P2, U2.5
SNSR_SCL1: R9.1, U5.P2, U6.5
SNSR_SCL2: R16.1, U8.P2, U9.5
SNSR_SCL3: R23.1, U11.P2, U12.5
SNSR_SCL4: R30.1, U14.P2, U15.5
SNSR_SCL5: R37.1, U17.P2, U18.5
SNSR_SCL6: R44.1, U20.P2, U21.5
SNSR_SCL7: R51.1, U23.P2, U24.5
SNSR_SCL8: R58.1, U26.P2, U27.5
SNSR_SCL9: R65.1, U29.P2, U30.5
SNSR_SCL10: R72.1, U32.P2, U33.5
SNSR_SCL11: R79.1, U35.P2, U36.5
SNSR_SCL12: R86.1, U38.P2, U39.5
SNSR_SCL13: R93.1, U41.P2, U42.5
SNSR_SCL14: R100.1, U44.P2, U45.5
SNSR_SCL15: R107.1, U47.P2, U48.5
SNSR_SCL16: R114.1, U50.P2, U51.5
SNSR_SCL17: R121.1, U53.P2, U54.5
SNSR_SCL18: R128.1, U56.P2, U57.5
SNSR_SCL19: R135.1, U59.P2, U60.5
SNSR_SCL20: R142.1, U62.P2, U63.5
SNSR_SCL21: R149.1, U65.P2, U66.5
SNSR_SCL22: R156.1, U68.P2, U69.5
SNSR_SCL23: R163.1, U71.P2, U72.5
SNSR_SCL24: R170.1, U74.P2, U75.5
SNSR_SDA: R1.1, U1.P3, U2.14
SNSR_SDA1: R8.1, U5.P3, U6.14
SNSR_SDA2: R15.1, U8.P3, U9.14
SNSR_SDA3: R22.1, U11.P3, U12.14
SNSR_SDA4: R29.1, U14.P3, U15.14
SNSR_SDA5: R36.1, U17.P3, U18.14
SNSR_SDA6: R43.1, U20.P3, U21.14
SNSR_SDA7: R50.1, U23.P3, U24.14
SNSR_SDA8: R57.1, U26.P3, U27.14
SNSR_SDA9: R64.1, U29.P3, U30.14
SNSR_SDA10: R71.1, U32.P3, U33.14
SNSR_SDA11: R78.1, U35.P3, U36.14
SNSR_SDA12: R85.1, U38.P3, U39.14
SNSR_SDA13: R92.1, U41.P3, U42.14
SNSR_SDA14: R99.1, U44.P3, U45.14
SNSR_SDA15: R106.1, U47.P3, U48.14
SNSR_SDA16: R113.1, U50.P3, U51.14
SNSR_SDA17: R120.1, U53.P3, U54.14
SNSR_SDA18: R127.1, U56.P3, U57.14
SNSR_SDA19: R134.1, U59.P3, U60.14
SNSR_SDA20: R141.1, U62.P3, U63.14
SNSR_SDA21: R148.1, U65.P3, U66.14
SNSR_SDA22: R155.1, U68.P3, U69.14
SNSR_SDA23: R162.1, U71.P3, U72.14
SNSR_SDA24: R169.1, U74.P3, U75.14

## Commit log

2019-02-01 Initial commit - file structure, some part creation
2019-02-05 Adds parts from temp lib to check parts.
2019-02-05 Adds a few parts (end of day merge)
2019-02-06 Adds parts to DC-DC converter
2019-02-07 Many traces and parts have been added, too many to list.
2019-02-08 Adds slik, trace work complete, ground vias added throughout design, schematic organized with lables
2019-02-11 Moves silk labels around
2019-02-11 Pushes temp lib to SparkFun Eagle Libraries and replaces parts in design with those parts
2019-02-14 Fixes slik labels on bottom, adjusts traces on Oscillator and reset line, changes ground vias to 10 mil
2019-02-14 Adds dimensions and special ordering instructions, adds text to MAX30101 that lists voltage ranges and I2C addresses
2019-02-15 Clarifies "Address" text underneath MAX32664 symbol in schematic by adding "I2C"
2019-02-15 Adds Production Files
2019-03-06 Deletes production files that were affected by DRC when they were panelized (more changes in description)
    * Adds new production files
    * Updates footprint of the Bio Sensor with new silk to outline part and has a bigger polarity marker
2019-08-05 Adds firmware to repo
2019-08-06 Removes Buzzard Lables and updates readme
2019-08-06 Fixes link in readme
2019-09-13 Update SparkFun_Pulse_Oximeter_Heart-Rate_Sensor.brd
    - Spelling Error =P
    - Turn on Measurements to show Board Dimensions
2019-09-13 Create Pulse_Oximeter_Heart_Rate_Sensor_Dimensions.png
    - add dimensions from Eagle files
2019-09-13 Adjust Dimensions layer for Documentation
    - Turn off layers for dimensions so less noisy
2023-03-22 Updates silk, updates bio sensor hub to slightly improved package, rolls version to v11
    * Updates schematic to include part numbers on all parts
    * Updates notes on parts
    * Updates package size on 0402 components to 0402-tight
    * Adds more vias
    * Adds more measures
2023-03-22 Adds new panel
2023-03-22 Changes note on finish to ENIG

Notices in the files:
parts and their libraries:
SparkFun-Aesthetics: Licensing: Creative Commons ShareAlike 4.0 International - https://creativecommons.org/licenses/by-sa/4.0
SparkFun-Aesthetics: Released under the Creative Commons Attribution Share-Alike 4.0 License
SparkFun-Aesthetics: https://creativecommons.org/licenses/by-sa/4.0
